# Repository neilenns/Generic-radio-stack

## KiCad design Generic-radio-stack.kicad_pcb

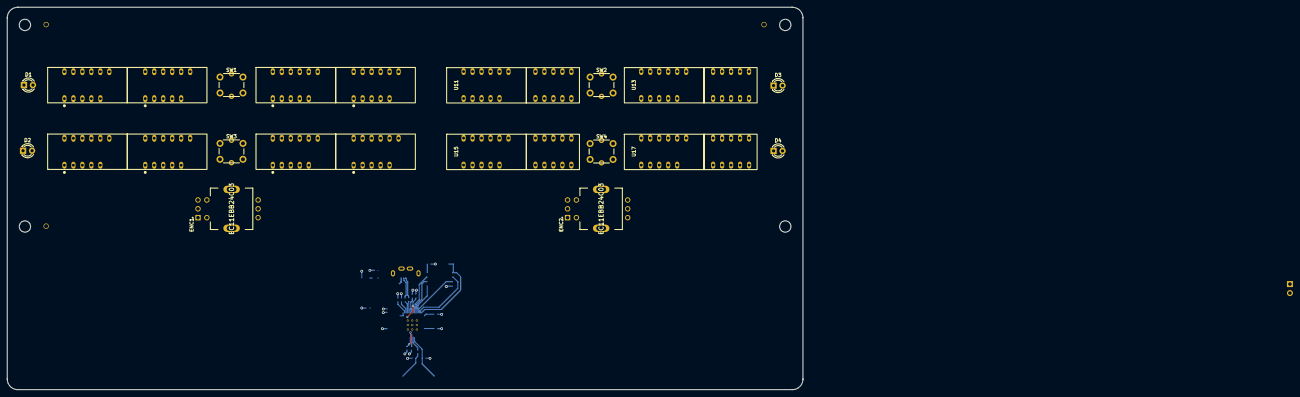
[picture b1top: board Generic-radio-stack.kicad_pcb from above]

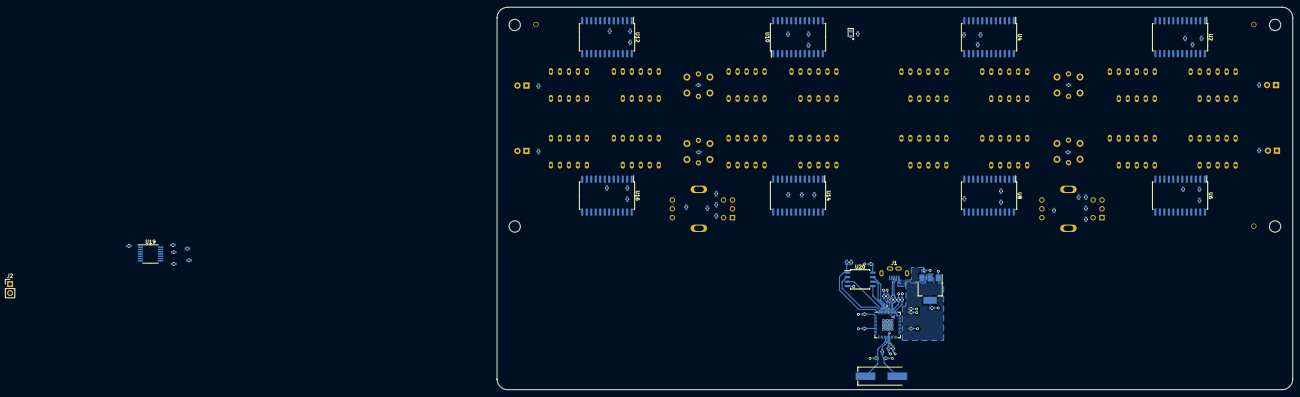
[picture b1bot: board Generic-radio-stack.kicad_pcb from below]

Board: 2 copper layers, 225.0 x 108.1 mm, 111 parts (86 on the bottom side), 175 nets.

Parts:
C1, C2, C3, C5, C7, C9, C11, C13, C15, C17: 10uF; Perfect_0402
C4, C6, C8, C10, C12, C14, C16, C18, C21, C22, C25, C26, C27, C28, C29, C30, C31, C32: 100nF; Perfect_0402
C19, C20: 27p; Perfect_0402
C23, C24: 1uF; Perfect_0402
D1, D2, D3, D4: GREEN; LED_D3.0mm
D5: LED_Small; LED_0603_1608Metric
ENC1, ENC2: EC11EBB24C03; ALPS-EC11EBB24C03-0
H1, H2, H3, H4: MountingHole; MountingHole_3.2mm_M3
H5, H6, H7: MountingHole; JLCPCB_Tooling_Hole
J1: USB_B_Micro; ZX80-B-5P
J2: Conn_01x02; PinHeader_1x02_P2.54mm_Vertical
R1, R2, R3, R4, R5, R6, R7, R8, R9, R28, R33: 1k; Perfect_0402
R10, R11, R12, R13, R14, R15, R16, R17: R_Small; Perfect_0402
R18, R19, R20, R21, R22, R23, R24, R25, R26, R27, R35: 10k; Perfect_0402
R29, R30: 27; Perfect_0402
R31, R32, R34: 197; Perfect_0402
R36, R37, R38: 310; Perfect_0402
SW1, SW2, SW3, SW4: SW_Push_LED; SW_PUSH_6mm
U1: NCP1117-3.3_SOT223; SOT-223-3_TabPin2
U2, U4, U6, U8, U10, U12, U14, U16: MAX7219; SOIC-24W_7.5x15.4mm_P1.27mm
U3, U5, U7, U9: 6_digit_7_segment_display_1; 6 digit (3+3) 7 segment LED display
U11, U13, U15, U17: 5_digit_7_segment_display; 5 digit (3+2) 7 segment LED display
U18: RP2040; RP2040-QFN-56
U19: LSF0204PWR; TSSOP-14_4.4x5mm_P0.65mm
U20: W25Q128JVS; SOIC-8_5.23x5.23mm_P1.27mm
Y1: ABLS-12.000MHZ-B4-T; Crystal_SMD_HC49-US

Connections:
+1V1: C21.1, C22.1, C23.1, U18.23 (DVDD), U18.45 (VREG_VOUT), U18.50 (DVDD)
+3V3: C2.1, C24.1, C25.1, C26.1, C27.1, C28.1, C29.1, C30.1, C31.1, C32.1, R5.1, R18.1, R19.1, R20.1, R21.1, R22.1, R23.1, R24.1, R25.1, R26.1, R27.1, R31.1, R32.1, R34.1, R35.1, U1.2 (VO), U18.1 (IOVDD), U18.10 (IOVDD), U18.22 (IOVDD), U18.33 (IOVDD), U18.42 (IOVDD), U18.43 (ADC_AVDD), U18.44 (VREG_IN), U18.48 (USB_VDD), U18.49 (IOVDD), U19.1 (Vref_A), U19.8 (EN), U20.8 (VCC)
+5V: C1.1, C3.1, C4.1, C5.1, C6.1, C7.1, C8.1, C9.1, C10.1, C11.1, C12.1, C13.1, C14.1, C15.1, C16.1, C17.1, C18.1, J1.1 (VBUS), R36.1, R37.1, R38.1, U1.3 (VI), U2.19 (V+), U4.19 (V+), U6.19 (V+), U8.19 (V+), U10.19 (V+), U12.19 (V+), U14.19 (V+), U16.19 (V+), U19.14 (Vref_B)
/5-digit display1/A: U12.14 (SEG_A), U13.11 (A), U13.19 (A')
/5-digit display1/B: U12.16 (SEG_B), U13.7 (B), U13.20 (B')
/5-digit display1/C: U12.20 (SEG_C), U13.4 (C), U13.15 (C')
/5-digit display1/D: U12.23 (SEG_D), U13.2 (D), U13.14 (D')
/5-digit display1/DIG_0: U12.2 (DIG_0), U13.18 (DIG2')
/5-digit display1/DIG_1: U12.11 (DIG_1), U13.21 (DIG1')
/5-digit display1/DIG_2: U12.6 (DIG_2), U13.8 (DIG3)
/5-digit display1/DIG_3: U12.7 (DIG_3), U13.9 (DIG2)
/5-digit display1/DIG_4: U12.3 (DIG_4), U13.12 (DIG1)
/5-digit display1/DOUT: U6.1 (DIN), U12.24 (DOUT)
/5-digit display1/DP: U12.22 (SEG_DP), U13.3 (DP), U13.17 (DP')
/5-digit display1/E: U12.21 (SEG_E), U13.1 (E), U13.13 (E')
/5-digit display1/F: U12.15 (SEG_F), U13.10 (F), U13.22 (F')
/5-digit display1/G: U12.17 (SEG_G), U13.5 (G), U13.16 (G')
/5-digit display2/A: U16.14 (SEG_A), U17.11 (A), U17.19 (A')
/5-digit display2/B: U16.16 (SEG_B), U17.7 (B), U17.20 (B')
/5-digit display2/C: U16.20 (SEG_C), U17.4 (C), U17.15 (C')
/5-digit display2/D: U16.23 (SEG_D), U17.2 (D), U17.14 (D')
/5-digit display2/DIG_0: U16.2 (DIG_0), U17.18 (DIG2')
/5-digit display2/DIG_1: U16.11 (DIG_1), U17.21 (DIG1')
/5-digit display2/DIG_2: U16.6 (DIG_2), U17.8 (DIG3)
/5-digit display2/DIG_3: U16.7 (DIG_3), U17.9 (DIG2)
/5-digit display2/DIG_4: U16.3 (DIG_4), U17.12 (DIG1)
/5-digit display2/DIN: U14.24 (DOUT), U16.1 (DIN)
/5-digit display2/DP: U16.22 (SEG_DP), U17.3 (DP), U17.17 (DP')
/5-digit display2/E: U16.21 (SEG_E), U17.1 (E), U17.13 (E')
/5-digit display2/F: U16.15 (SEG_F), U17.10 (F), U17.22 (F')
/5-digit display2/G: U16.17 (SEG_G), U17.5 (G), U17.16 (G')
/5-digit display3/A: U14.14 (SEG_A), U15.11 (A), U15.19 (A')
/5-digit display3/B: U14.16 (SEG_B), U15.7 (B), U15.20 (B')
/5-digit display3/C: U14.20 (SEG_C), U15.4 (C), U15.15 (C')
/5-digit display3/D: U14.23 (SEG_D), U15.2 (D), U15.14 (D')
/5-digit display3/DIG_0: U14.2 (DIG_0), U15.18 (DIG2')
/5-digit display3/DIG_1: U14.11 (DIG_1), U15.21 (DIG1')
/5-digit display3/DIG_2: U14.6 (DIG_2), U15.8 (DIG3)
/5-digit display3/DIG_3: U14.7 (DIG_3), U15.9 (DIG2)
/5-digit display3/DIG_4: U14.3 (DIG_4), U15.12 (DIG1)
/5-digit display3/DIN: U8.24 (DOUT), U14.1 (DIN)
/5-digit display3/DP: U14.22 (SEG_DP), U15.3 (DP), U15.17 (DP')
/5-digit display3/E: U14.21 (SEG_E), U15.1 (E), U15.13 (E')
/5-digit display3/F: U14.15 (SEG_F), U15.10 (F), U15.22 (F')
/5-digit display3/G: U14.17 (SEG_G), U15.5 (G), U15.16 (G')
/5-digit display/A: U10.14 (SEG_A), U11.11 (A), U11.19 (A')
/5-digit display/B: U10.16 (SEG_B), U11.7 (B), U11.20 (B')
/5-digit display/C: U10.20 (SEG_C), U11.4 (C), U11.15 (C')
/5-digit display/D: U10.23 (SEG_D), U11.2 (D), U11.14 (D')
/5-digit display/DIG_0: U10.2 (DIG_0), U11.18 (DIG2')
/5-digit display/DIG_1: U10.11 (DIG_1), U11.21 (DIG1')
/5-digit display/DIG_2: U10.6 (DIG_2), U11.8 (DIG3)
/5-digit display/DIG_3: U10.7 (DIG_3), U11.9 (DIG2)
/5-digit display/DIG_4: U10.3 (DIG_4), U11.12 (DIG1)
/5-digit display/DIN: U4.24 (DOUT), U10.1 (DIN)
/5-digit display/DOUT: U10.24 (DOUT), U12.1 (DIN)
/5-digit display/DP: U10.22 (SEG_DP), U11.3 (DP), U11.17 (DP')
/5-digit display/E: U10.21 (SEG_E), U11.1 (E), U11.13 (E')
/5-digit display/F: U10.15 (SEG_F), U11.10 (F), U11.22 (F')
/5-digit display/G: U10.17 (SEG_G), U11.5 (G), U11.16 (G')
/6-digit display1/A: U4.14 (SEG_A), U5.11 (A), U5.23 (A')
/6-digit display1/B: U4.16 (SEG_B), U5.7 (B), U5.19 (B')
/6-digit display1/C: U4.20 (SEG_C), U5.4 (C), U5.16 (C')
/6-digit display1/D: U4.23 (SEG_D), U5.2 (D), U5.14 (D')
/6-digit display1/DIG_0: U4.2 (DIG_0), U5.20 (DIG3')
/6-digit display1/DIG_1: U4.11 (DIG_1), U5.21 (DIG2')
/6-digit display1/DIG_2: U4.6 (DIG_2), U5.24 (DIG1')
/6-digit display1/DIG_3: U4.7 (DIG_3), U5.8 (DIG3)
/6-digit display1/DIG_4: U4.3 (DIG_4), U5.9 (DIG2)
/6-digit display1/DIG_5: U4.10 (DIG_5), U5.12 (DIG1)
/6-digit display1/DP: U4.22 (SEG_DP), U5.3 (DP), U5.15 (DP')
/6-digit display1/E: U4.21 (SEG_E), U5.1 (E), U5.13 (E')
/6-digit display1/F: U4.15 (SEG_F), U5.10 (F), U5.22 (F')
/6-digit display1/G: U4.17 (SEG_G), U5.5 (G), U5.17 (G')
/6-digit display2/A: U6.14 (SEG_A), U7.11 (A), U7.23 (A')
/6-digit display2/B: U6.16 (SEG_B), U7.7 (B), U7.19 (B')
/6-digit display2/C: U6.20 (SEG_C), U7.4 (C), U7.16 (C')
/6-digit display2/D: U6.23 (SEG_D), U7.2 (D), U7.14 (D')
/6-digit display2/DIG_0: U6.2 (DIG_0), U7.20 (DIG3')
/6-digit display2/DIG_1: U6.11 (DIG_1), U7.21 (DIG2')
/6-digit display2/DIG_2: U6.6 (DIG_2), U7.24 (DIG1')
/6-digit display2/DIG_3: U6.7 (DIG_3), U7.8 (DIG3)
/6-digit display2/DIG_4: U6.3 (DIG_4), U7.9 (DIG2)
/6-digit display2/DIG_5: U6.10 (DIG_5), U7.12 (DIG1)
/6-digit display2/DOUT: U6.24 (DOUT), U8.1 (DIN)
/6-digit display2/DP: U6.22 (SEG_DP), U7.3 (DP), U7.15 (DP')
/6-digit display2/E: U6.21 (SEG_E), U7.1 (E), U7.13 (E')
/6-digit display2/F: U6.15 (SEG_F), U7.10 (F), U7.22 (F')
/6-digit display2/G: U6.17 (SEG_G), U7.5 (G), U7.17 (G')
/6-digit display3/A: U8.14 (SEG_A), U9.11 (A), U9.23 (A')
/6-digit display3/B: U8.16 (SEG_B), U9.7 (B), U9.19 (B')
/6-digit display3/C: U8.20 (SEG_C), U9.4 (C), U9.16 (C')
/6-digit display3/D: U8.23 (SEG_D), U9.2 (D), U9.14 (D')
/6-digit display3/DIG_0: U8.2 (DIG_0), U9.20 (DIG3')
/6-digit display3/DIG_1: U8.11 (DIG_1), U9.21 (DIG2')
/6-digit display3/DIG_2: U8.6 (DIG_2), U9.24 (DIG1')
/6-digit display3/DIG_3: U8.7 (DIG_3), U9.8 (DIG3)
/6-digit display3/DIG_4: U8.3 (DIG_4), U9.9 (DIG2)
/6-digit display3/DIG_5: U8.10 (DIG_5), U9.12 (DIG1)
/6-digit display3/DP: U8.22 (SEG_DP), U9.3 (DP), U9.15 (DP')
/6-digit display3/E: U8.21 (SEG_E), U9.1 (E), U9.13 (E')
/6-digit display3/F: U8.15 (SEG_F), U9.10 (F), U9.22 (F')
/6-digit display3/G: U8.17 (SEG_G), U9.5 (G), U9.17 (G')
/6-digit display/A: U2.14 (SEG_A), U3.11 (A), U3.23 (A')
/6-digit display/B: U2.16 (SEG_B), U3.7 (B), U3.19 (B')
/6-digit display/C: U2.20 (SEG_C), U3.4 (C), U3.16 (C')
/6-digit display/D: U2.23 (SEG_D), U3.2 (D), U3.14 (D')
/6-digit display/DIG_0: U2.2 (DIG_0), U3.20 (DIG3')
/6-digit display/DIG_1: U2.11 (DIG_1), U3.21 (DIG2')
/6-digit display/DIG_2: U2.6 (DIG_2), U3.24 (DIG1')
/6-digit display/DIG_3: U2.7 (DIG_3), U3.8 (DIG3)
/6-digit display/DIG_4: U2.3 (DIG_4), U3.9 (DIG2)
/6-digit display/DIG_5: U2.10 (DIG_5), U3.12 (DIG1)
/6-digit display/DOUT: U2.24 (DOUT), U4.1 (DIN)
/6-digit display/DP: U2.22 (SEG_DP), U3.3 (DP), U3.15 (DP')
/6-digit display/E: U2.21 (SEG_E), U3.1 (E), U3.13 (E')
/6-digit display/F: U2.15 (SEG_F), U3.10 (F), U3.22 (F')
/6-digit display/G: U2.17 (SEG_G), U3.5 (G), U3.17 (G')
/RP2040/D+: R29.1, U18.47 (USB_DP)
/RP2040/D-: R30.1, U18.46 (USB_DM)
/RP2040/QSPI_SCLK: U18.52 (QSPI_SCLK), U20.6 (CLK)
/RP2040/QSPI_SD0: U18.53 (QSPI_SD0), U20.5 (DI(IO0))
/RP2040/QSPI_SD1: U18.55 (QSPI_SD1), U20.2 (DO(IO1))
/RP2040/QSPI_SD2: U18.54 (QSPI_SD2), U20.3 (IO2)
/RP2040/QSPI_SD3: U18.51 (QSPI_SD3), U20.7 (IO3)
/RP2040/QSPI_SS: R33.2, R35.2, U18.56 (QSPI_SS), U20.1 (~CS)
/RP2040/XIN: C19.2, U18.20 (XIN), Y1.1
/RP2040/XOUT: R28.2, U18.21 (XOUT)
/RP2040/~USB_BOOT: J2.1, R33.1
COM1_INPUT: R1.1, U18.2 (GPIO0)
COM1_XFR: SW1.2, U18.28 (GPIO17)
COM1_XFR_LED: R6.1, U18.34 (GPIO22)
COM2_INPUT: R2.1, U18.3 (GPIO1)
COM2_XFR: SW3.2, U18.29 (GPIO18)
COM2_XFR_LED: R8.1, U18.35 (GPIO23)
COM_A: ENC1.8 (A), R21.2, U18.9 (GPIO7)
COM_A': ENC1.1 (A'), R20.2, U18.12 (GPIO9)
COM_B: ENC1.10 (B), R19.2, U18.11 (GPIO8)
COM_B': ENC1.3 (B'), R18.2, U18.13 (GPIO10)
COM_BUTTON: ENC1.4 (D), R22.2, U18.14 (GPIO11)
D+: J1.3 (D+), R29.2
D-: J1.2 (D-), R30.2
GND: C1.2, C2.2, C3.2, C4.2, C5.2, C6.2, C7.2, C8.2, C9.2, C10.2, C11.2, C12.2, C13.2, C14.2, C15.2, C16.2, C17.2, C18.2, C19.1, C20.1, C21.2, C22.2, C23.2, C24.2, C25.2, C26.2, C27.2, C28.2, C29.2, C30.2, C31.2, C32.2, D1.1 (K), D2.1 (K), D3.1 (K), D4.1 (K), D5.1 (K), ENC1.2 (C'), ENC1.5 (E), ENC1.9 (C), ENC2.2 (C'), ENC2.5 (E), ENC2.9 (C), J1.5 (GND), J1.6 (Shield), J2.2, R10.2, R11.2, R12.2, R13.2, R14.2, R15.2, R16.2, R17.2, SW1.1, SW1.4, SW2.1, SW2.4, SW3.1, SW3.4, SW4.1, SW4.4, U1.1 (GND), U2.4 (GND), U2.9 (GND), U4.4 (GND), U4.9 (GND), U6.4 (GND), U6.9 (GND), U8.4 (GND), U8.9 (GND), U10.4 (GND), U10.9 (GND), U12.4 (GND), U12.9 (GND), U14.4 (GND), U14.9 (GND), U16.4 (GND), U16.9 (GND), U18.19 (TESTEN), U18.57 (GND), U19.7 (GND), U20.4 (GND)
LED_CLOCK: R32.2, R37.2, U2.13 (CLK), U4.13 (CLK), U6.13 (CLK), U8.13 (CLK), U10.13 (CLK), U12.13 (CLK), U14.13 (CLK), U16.13 (CLK), U18.7 (GPIO5), U19.3 (A2), U19.12 (B2)
LED_DATA: R34.2, R36.2, U2.1 (DIN), U18.6 (GPIO4), U19.2 (A1), U19.13 (B1)
LED_LOAD: R31.2, R38.2, U2.12 (LOAD), U4.12 (LOAD), U6.12 (LOAD), U8.12 (LOAD), U10.12 (LOAD), U12.12 (LOAD), U14.12 (LOAD), U16.12 (LOAD), U18.8 (GPIO6), U19.4 (A3), U19.11 (B3)
NAV1_INPUT: R3.1, U18.4 (GPIO2)
NAV1_XFR: SW2.2, U18.30 (GPIO19)
NAV1_XFR_LED: R7.1, U18.32 (GPIO21)
NAV2_INPUT: R4.1, U18.5 (GPIO3)
NAV2_XFR: SW4.2, U18.31 (GPIO20)
NAV2_XFR_LED: R9.1, U18.36 (GPIO24)
NAV_A: ENC2.8 (A), R26.2, U18.15 (GPIO12)
NAV_A': ENC2.1 (A'), R25.2, U18.17 (GPIO14)
NAV_B: ENC2.10 (B), R24.2, U18.16 (GPIO13)
NAV_B': ENC2.3 (B'), R23.2, U18.18 (GPIO15)
NAV_BUTTON: ENC2.4 (D), R27.2, U18.27 (GPIO16)
unnamed: C20.2, R28.1, Y1.2
unnamed: D1.2 (A), R1.2
unnamed: D2.2 (A), R2.2
unnamed: D3.2 (A), R3.2
unnamed: D4.2 (A), R4.2
unnamed: D5.2 (A), R5.2
unnamed: R6.2, SW1.3
unnamed: R7.2, SW2.3
unnamed: R8.2, SW3.3
unnamed: R9.2, SW4.3
unnamed: R10.1, U2.18 (ISET)
unnamed: R11.1, U4.18 (ISET)
unnamed: R12.1, U6.18 (ISET)
unnamed: R13.1, U8.18 (ISET)
unnamed: R14.1, U10.18 (ISET)
unnamed: R15.1, U12.18 (ISET)
unnamed: R16.1, U14.18 (ISET)
unnamed: R17.1, U16.18 (ISET)

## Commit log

2022-01-17 Initial work to get CI/CD working locally with KiCad 6
2022-01-17 Update extension for KiCad 6
2022-01-18 Use native KiBot replacement for date and version
2022-01-18 Add placeholders
2022-01-18 Basic stuff starting
2022-01-18 Add RP2040
2022-01-18 Bunch more schematic work
2022-01-18 Add display footprints and models
2022-01-18 Custom component for six digit display
2022-01-18 More footprint updates
2022-01-18 More footprint changes
2022-01-19 Board layout begins. Ugh.
2022-01-20 Added dual encoder 3d model, fit everything on the board
2022-01-20 Add mounting holes
2022-01-21 initial routing of RP2040
2022-01-21 More RP2040 routing
2022-01-24 New USB footprint
2025-02-25 Add renovate.json
